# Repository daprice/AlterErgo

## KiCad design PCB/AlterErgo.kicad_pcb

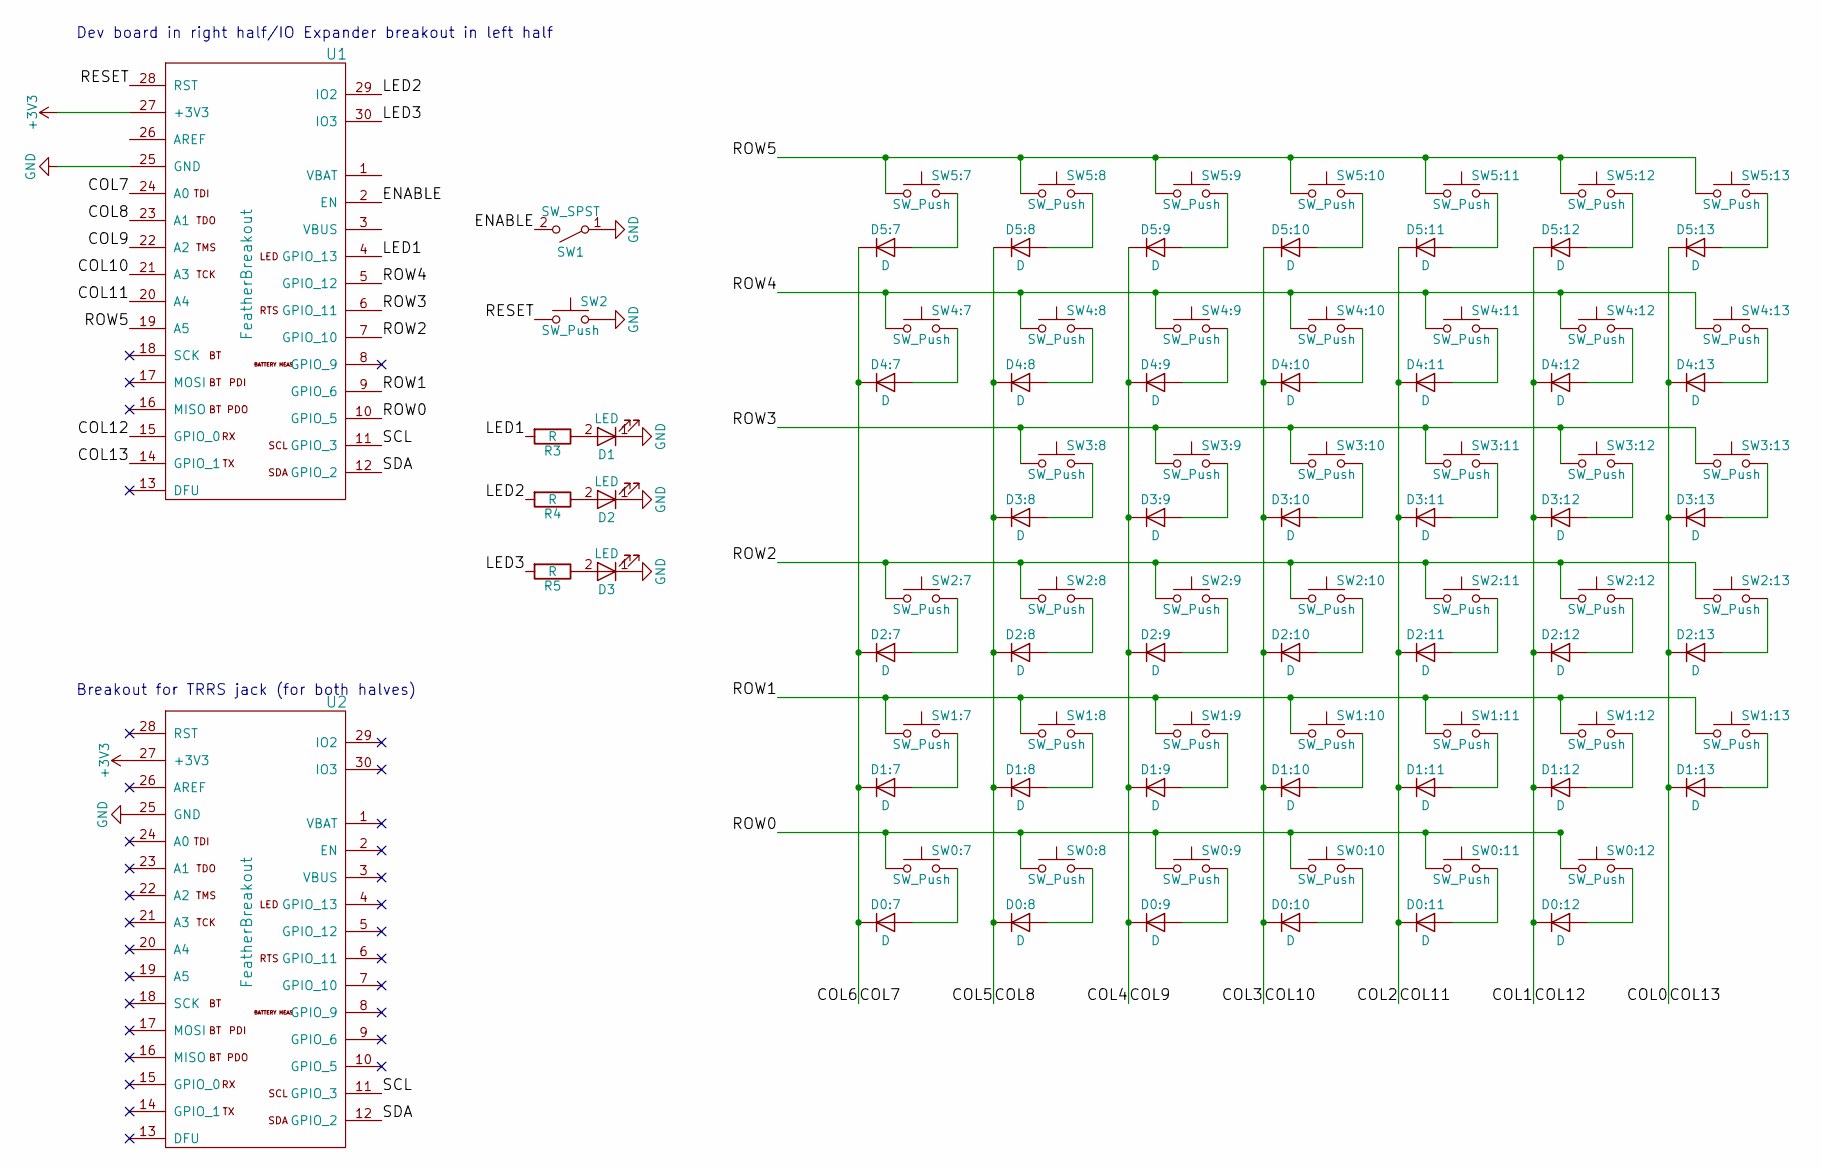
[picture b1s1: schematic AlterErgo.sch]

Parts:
D0:7, D0:8, D0:9, D0:10, D0:11, D0:12, D1:7, D1:8, D1:9, D1:10, D1:11, D1:12, D1:13, D2:7, D2:8, D2:9, D2:10, D2:11, D2:12, D2:13, D3:8, D3:9, D3:10, D3:11, D3:12, D3:13, D4:7, D4:8, D4:9, D4:10, D4:11, D4:12, D4:13, D5:7, D5:8, D5:9, D5:10, D5:11, D5:12, D5:13: D; D_SOD-123
D1, D2, D3: LED; LED_D3.0mm
R3, R4, R5: R; R_Axial_DIN0207_L6.3mm_D2.5mm_P7.62mm_Horizontal
SW0:7, SW0:8, SW0:9, SW0:10, SW0:11, SW0:12, SW1:7, SW1:8, SW1:9, SW1:10, SW1:11, SW1:12, SW1:13, SW2:7, SW2:8, SW2:9, SW2:10, SW2:11, SW2:12, SW2:13, SW3:8, SW3:9, SW3:10, SW3:11, SW3:12, SW3:13, SW4:7, SW4:8, SW4:9, SW4:10, SW4:11, SW4:12, SW4:13, SW5:7, SW5:8, SW5:9, SW5:10, SW5:11, SW5:12, SW5:13: SW_Push; Kailh_socket_optional_reversible
SW1: SW_SPST; GPTS_SPST_Pushbutton
SW2: SW_Push; SW_PUSH_6mm
U1, U2: FeatherBreakout

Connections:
+3V3: U1.27 (+3V3), U2.27 (+3V3)
/COL0: D1:13.1 (K), D2:13.1 (K), D3:13.1 (K), D4:13.1 (K), D5:13.1 (K), U1.14 (GPIO_1)
/COL1: D0:12.1 (K), D1:12.1 (K), D2:12.1 (K), D3:12.1 (K), D4:12.1 (K), D5:12.1 (K), U1.15 (GPIO_0)
/COL4: D0:9.1 (K), D1:9.1 (K), D2:9.1 (K), D3:9.1 (K), D4:9.1 (K), D5:9.1 (K), U1.22 (A2)
/COL5: D0:8.1 (K), D1:8.1 (K), D2:8.1 (K), D3:8.1 (K), D4:8.1 (K), D5:8.1 (K), U1.23 (A1)
/COL6: D0:7.1 (K), D1:7.1 (K), D2:7.1 (K), D4:7.1 (K), D5:7.1 (K), U1.24 (A0)
/COL10: D0:10.1 (K), D1:10.1 (K), D2:10.1 (K), D3:10.1 (K), D4:10.1 (K), D5:10.1 (K), U1.21 (A3)
/COL11: D0:11.1 (K), D1:11.1 (K), D2:11.1 (K), D3:11.1 (K), D4:11.1 (K), D5:11.1 (K), U1.20 (A4)
/ENABLE: SW1.2 (B), U1.2 (EN)
/LED1: R3.2, U1.4 (GPIO_13)
/LED2: R4.2, U1.29 (IO2)
/LED3: R5.2, U1.30 (IO3)
/RESET: SW2.1, U1.28 (RST)
/ROW0: SW0:7.1, SW0:8.1, SW0:9.1, SW0:10.1, SW0:11.1, SW0:12.1, U1.10 (GPIO_5); also elsewhere on the board
/ROW1: SW1:7.1, SW1:8.1, SW1:9.1, SW1:10.1, SW1:11.1, SW1:12.1, SW1:13.1, U1.9 (GPIO_6); also elsewhere on the board
/ROW2: SW2:7.1, SW2:8.1, SW2:9.1, SW2:10.1, SW2:11.1, SW2:12.1, SW2:13.1, U1.7 (GPIO_10); also elsewhere on the board
/ROW3: SW3:8.1, SW3:9.1, SW3:10.1, SW3:11.1, SW3:12.1, SW3:13.1, U1.6 (GPIO_11); also elsewhere on the board
/ROW4: SW4:7.1, SW4:8.1, SW4:9.1, SW4:10.1, SW4:11.1, SW4:12.1, SW4:13.1, U1.5 (GPIO_12); also elsewhere on the board
/ROW5: SW5:7.1, SW5:8.1, SW5:9.1, SW5:10.1, SW5:11.1, SW5:12.1, SW5:13.1, U1.19 (A5); also elsewhere on the board
/SCL: U1.11 (GPIO_3), U2.11 (GPIO_3)
/SDA: U1.12 (GPIO_2), U2.12 (GPIO_2)
GND: D1.1 (K), D2.1 (K), D3.1 (K), SW1.1 (A), SW2.2, U1.25 (GND), U2.25 (GND)
unnamed: D0:7.2 (A), SW0:7.2
unnamed: D0:8.2 (A), SW0:8.2
unnamed: D0:9.2 (A), SW0:9.2
unnamed 25: D0:10.2 (A), SW0:10.2; also elsewhere on the board
unnamed 26: D0:11.2 (A), SW0:11.2; also elsewhere on the board
unnamed: D0:12.2 (A), SW0:12.2
unnamed: D1.2 (A), R3.1
unnamed: D1:7.2 (A), SW1:7.2
unnamed: D1:8.2 (A), SW1:8.2
unnamed: D1:9.2 (A), SW1:9.2
unnamed: D1:10.2 (A), SW1:10.2
unnamed: D1:11.2 (A), SW1:11.2
unnamed: D1:12.2 (A), SW1:12.2
unnamed 35: D1:13.2 (A), SW1:13.2; also elsewhere on the board
unnamed: D2.2 (A), R4.1
unnamed: D2:7.2 (A), SW2:7.2
unnamed: D2:8.2 (A), SW2:8.2
unnamed: D2:9.2 (A), SW2:9.2
unnamed: D2:10.2 (A), SW2:10.2
unnamed: D2:11.2 (A), SW2:11.2
unnamed: D2:12.2 (A), SW2:12.2
unnamed 43: D2:13.2 (A), SW2:13.2; also elsewhere on the board
unnamed: D3.2 (A), R5.1
unnamed: D3:8.2 (A), SW3:8.2
unnamed: D3:9.2 (A), SW3:9.2
unnamed: D3:10.2 (A), SW3:10.2
unnamed: D3:11.2 (A), SW3:11.2
unnamed: D3:12.2 (A), SW3:12.2
unnamed 50: D3:13.2 (A), SW3:13.2; also elsewhere on the board
unnamed: D4:7.2 (A), SW4:7.2
unnamed: D4:8.2 (A), SW4:8.2
unnamed: D4:9.2 (A), SW4:9.2
unnamed: D4:10.2 (A), SW4:10.2
unnamed: D4:11.2 (A), SW4:11.2
unnamed: D4:12.2 (A), SW4:12.2
unnamed 57: D4:13.2 (A), SW4:13.2; also elsewhere on the board
unnamed: D5:7.2 (A), SW5:7.2
unnamed: D5:8.2 (A), SW5:8.2
unnamed: D5:9.2 (A), SW5:9.2
unnamed: D5:10.2 (A), SW5:10.2
unnamed: D5:11.2 (A), SW5:11.2
unnamed: D5:12.2 (A), SW5:12.2
unnamed 64: D5:13.2 (A), SW5:13.2; also elsewhere on the board

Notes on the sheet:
Dev board in right half/IO Expander breakout in left half
Breakout for TRRS jack (for both halves)

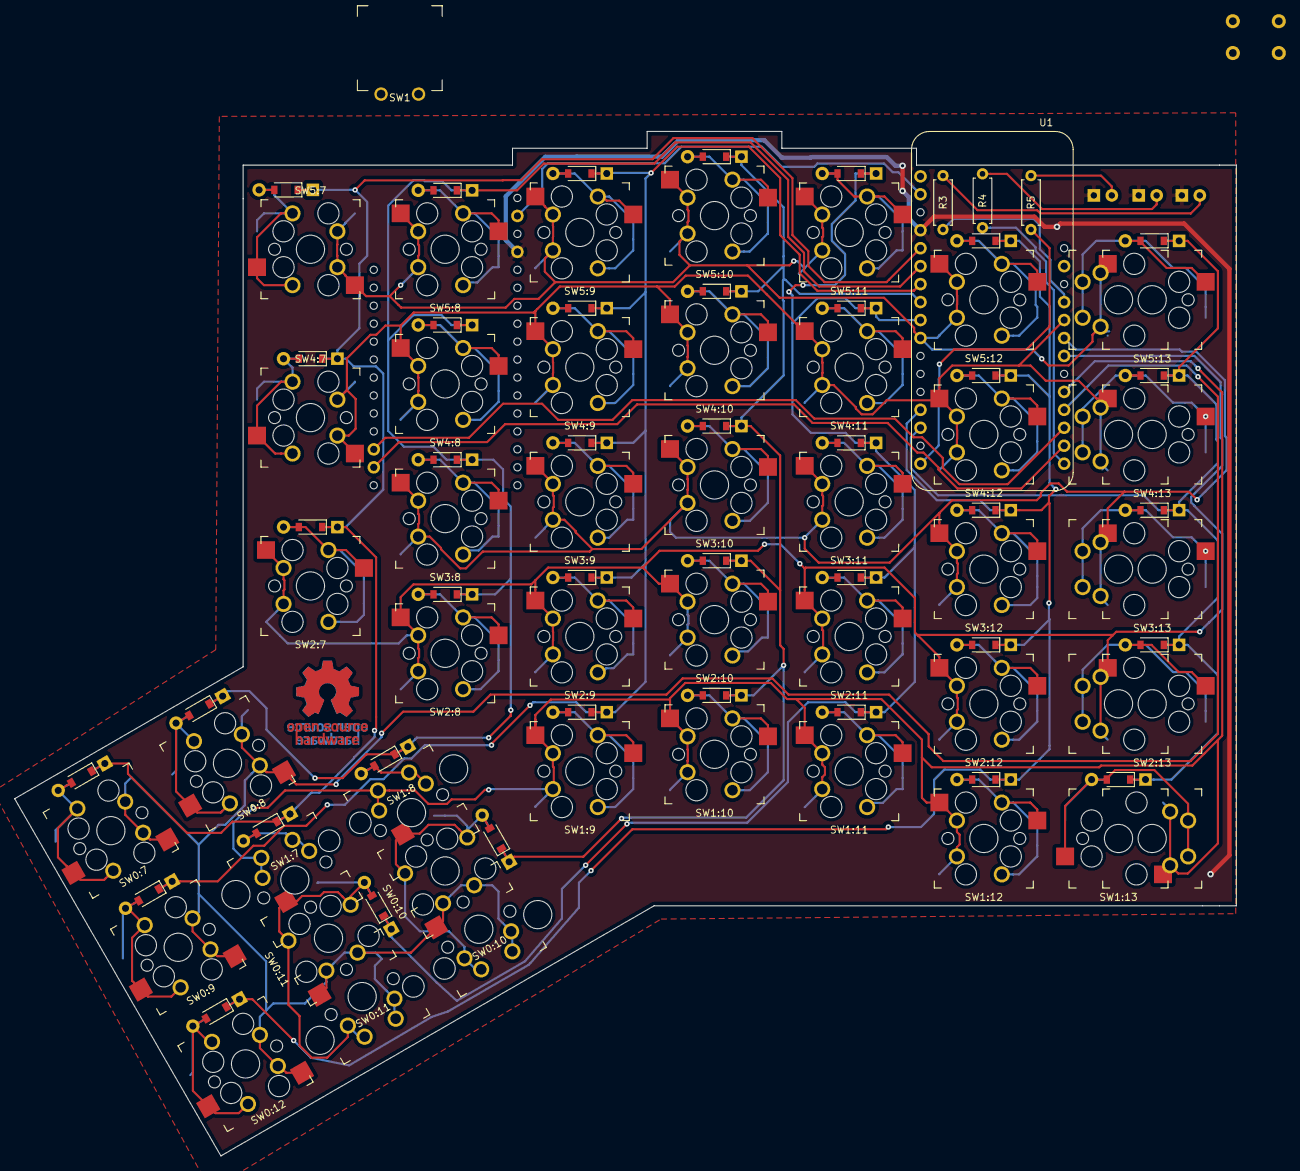
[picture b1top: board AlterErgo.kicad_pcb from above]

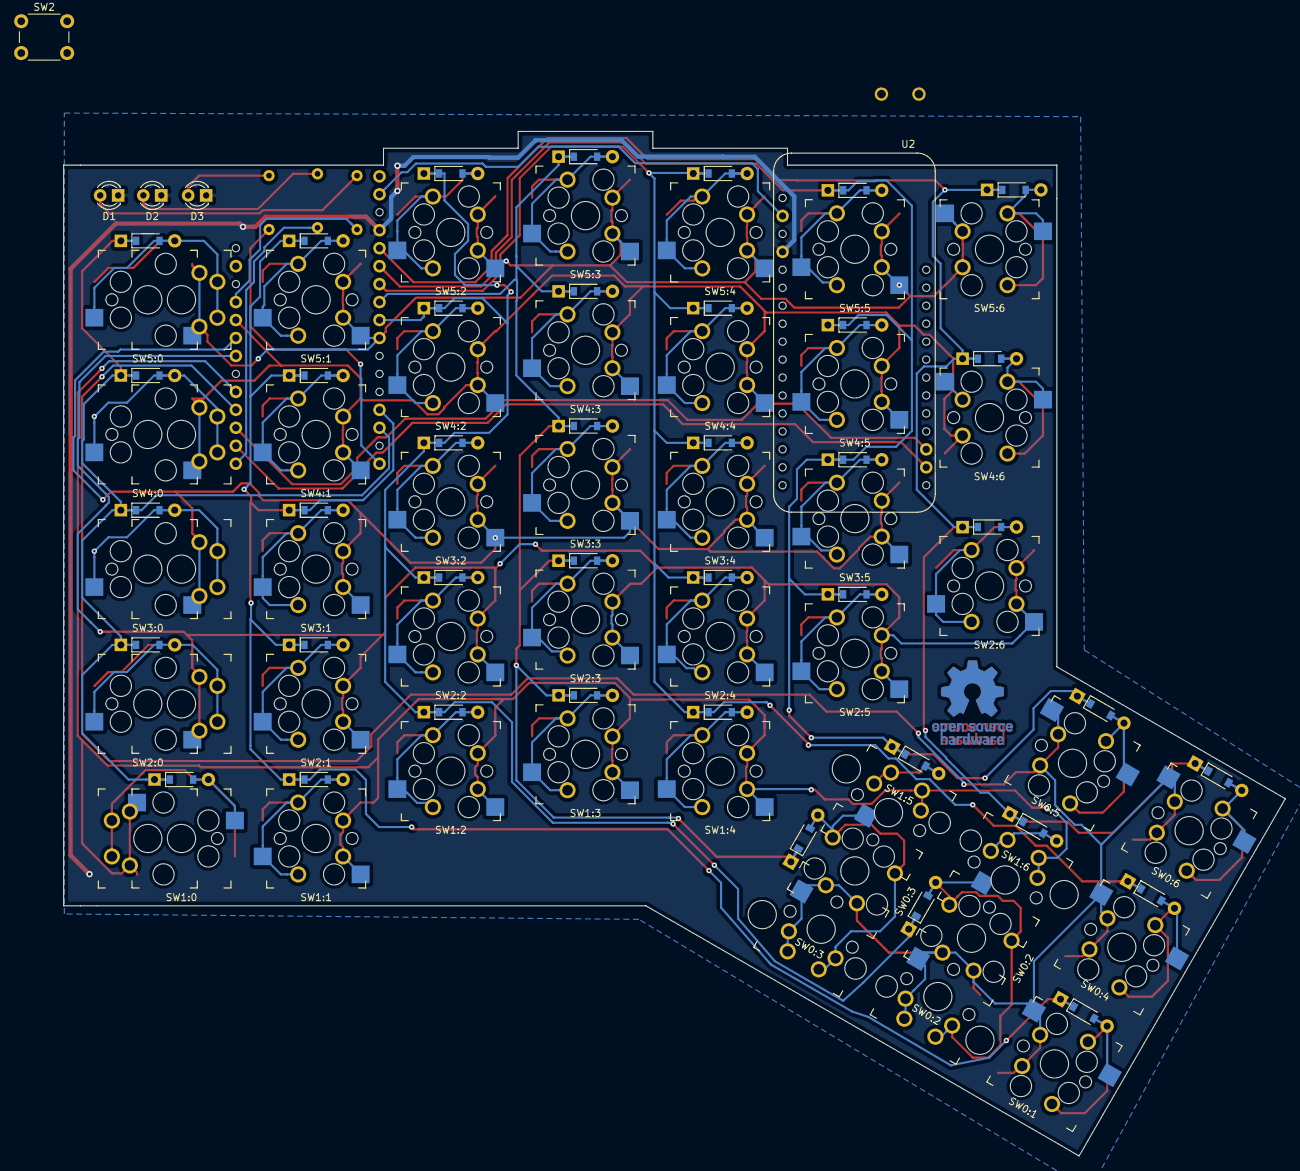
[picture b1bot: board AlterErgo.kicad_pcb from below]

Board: 2 copper layers, 172.8 x 144.9 mm, 99 parts (5 on the bottom side), 65 nets.

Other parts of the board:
SW0:10#2, SW0:11#2: SW_Push; MX_reversible
SW1:13#2, SW2:13#2, SW3:13#2, SW4:13#2, SW5:13#2: SW_Push; MX_reversible_minimal
Stab0:10, Stab0:11: SW_Stabilizer; MX_Stabilizer_2u

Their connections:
/ROW0: SW0:10#2.1, SW0:11#2.1; also elsewhere on the board
/ROW1: SW1:13#2.1; also elsewhere on the board
/ROW2: SW2:13#2.1; also elsewhere on the board
/ROW3: SW3:13#2.1; also elsewhere on the board
/ROW4: SW4:13#2.1; also elsewhere on the board
/ROW5: SW5:13#2.1; also elsewhere on the board
unnamed 25: SW0:10#2.2; also elsewhere on the board
unnamed 26: SW0:11#2.2; also elsewhere on the board
unnamed 35: SW1:13#2.2; also elsewhere on the board
unnamed 43: SW2:13#2.2; also elsewhere on the board
unnamed 50: SW3:13#2.2; also elsewhere on the board
unnamed 57: SW4:13#2.2; also elsewhere on the board
unnamed 64: SW5:13#2.2; also elsewhere on the board

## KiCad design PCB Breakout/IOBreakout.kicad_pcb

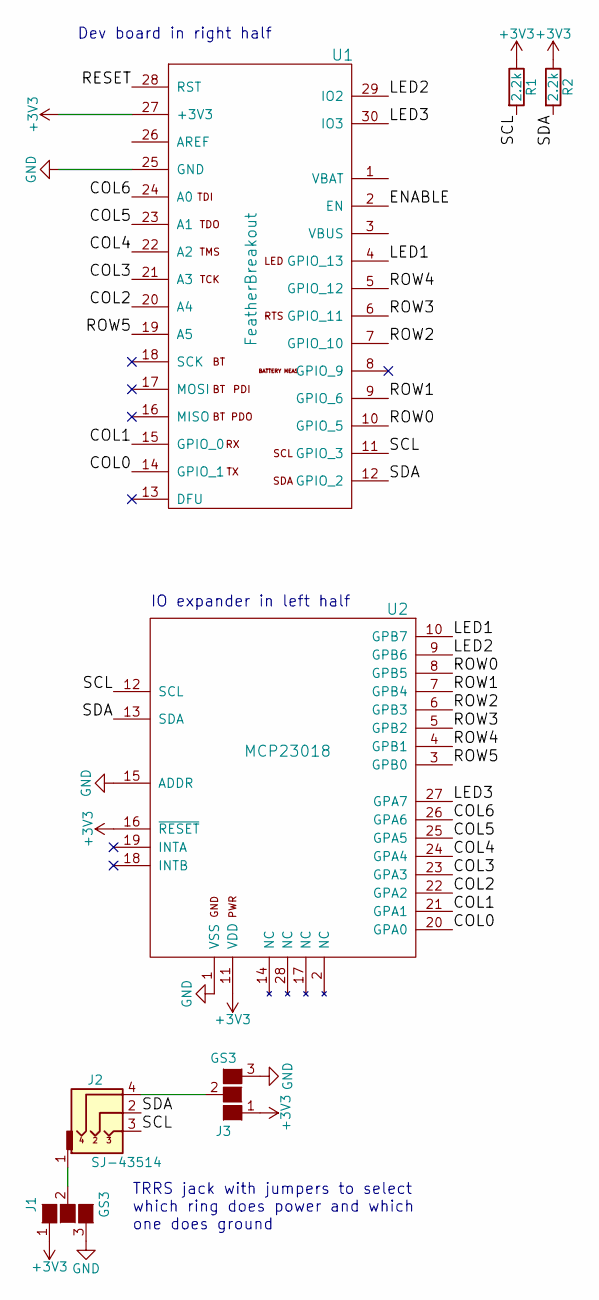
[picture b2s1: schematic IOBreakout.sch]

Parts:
J1, J3: GS3
J2: SJ-43514; TRRS_Jack_SJ-43514_reversible
R1, R2: 2.2k; R_Axial_DIN0207_L6.3mm_D2.5mm_P7.62mm_Horizontal
U1: FeatherBreakout
U2: MCP23018; DIP-28_W7.62mm

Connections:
+3V3: J1.1 (G1), J3.1 (G1), R1.1, R2.1, U1.27 (+3V3), U2.11 (VDD), U2.16 (~RESET)
/COL0: U1.14 (GPIO_1), U2.20 (GPA0)
/COL1: U1.15 (GPIO_0), U2.21 (GPA1)
/COL2: U1.20 (A4), U2.22 (GPA2)
/COL3: U1.21 (A3), U2.23 (GPA3)
/COL4: U1.22 (A2), U2.24 (GPA4)
/COL5: U1.23 (A1), U2.25 (GPA5)
/COL6: U1.24 (A0), U2.26 (GPA6)
/ENABLE: U1.2 (EN)
/LED1: U1.4 (GPIO_13), U2.10 (GPB7)
/LED2: U1.29 (IO2), U2.9 (GPB6)
/LED3: U1.30 (IO3), U2.27 (GPA7)
/RESET: U1.28 (RST)
/ROW0: U1.10 (GPIO_5), U2.8 (GPB5)
/ROW1: U1.9 (GPIO_6), U2.7 (GPB4)
/ROW2: U1.7 (GPIO_10), U2.6 (GPB3)
/ROW3: U1.6 (GPIO_11), U2.5 (GPB2)
/ROW4: U1.5 (GPIO_12), U2.4 (GPB1)
/ROW5: U1.19 (A5), U2.3 (GPB0)
/SCL: J2.3, R1.2, U1.11 (GPIO_3), U2.12 (SCL)
/SDA: J2.2, R2.2, U1.12 (GPIO_2), U2.13 (SDA)
GND: J1.3 (G3), J3.3 (G3), U1.25 (GND), U2.1 (VSS), U2.15 (ADDR)
unnamed: J1.2 (G2), J2.1
unnamed: J2.4, J3.2 (G2)

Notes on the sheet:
TRRS jack with jumpers to select which ring does power and which one does ground
IO expander in left half
Dev board in right half

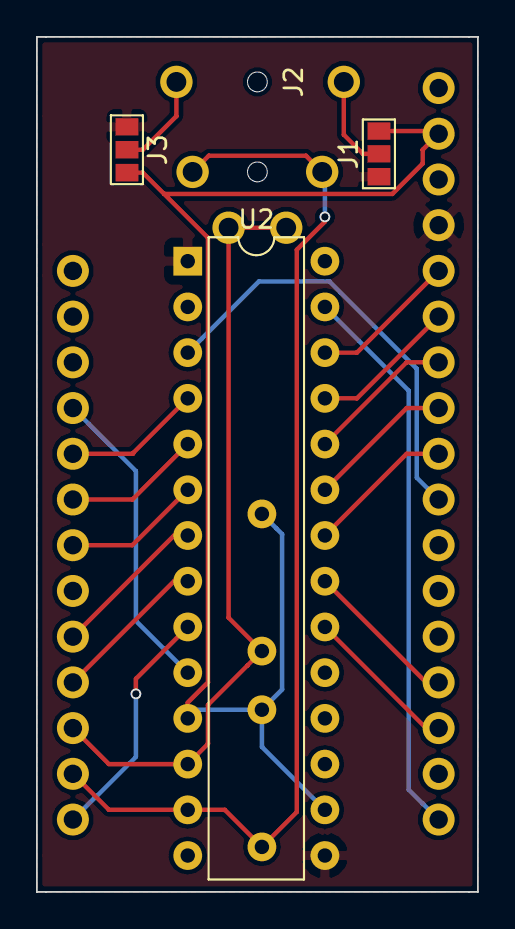
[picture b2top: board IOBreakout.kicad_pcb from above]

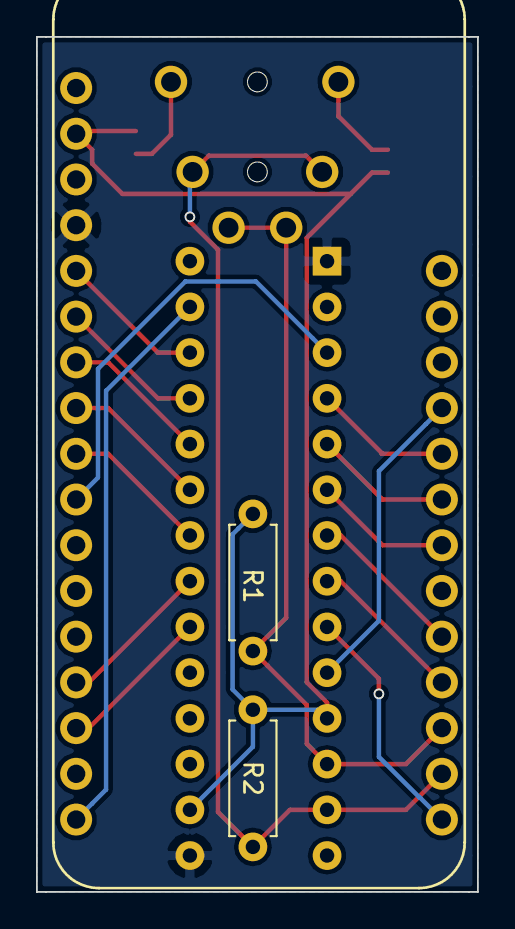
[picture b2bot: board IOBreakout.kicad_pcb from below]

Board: 2 copper layers, 24.5 x 47.5 mm, 7 parts (3 on the bottom side), 22 nets.

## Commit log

2018-03-27 Design key matrix and add necessary IC schematics
2018-04-03 Add TRRS jack to schematic; annotate matrix diodes
2018-04-09 Add .gitignore
2018-04-09 Associate most components with footprints
2018-05-15 Assign all components to footprints; generate netlist
2018-06-12 Position non-angled switches on PCB
2018-06-13 Position thumb cluster switches;
    The formulas I used to convert from Keyboard Layout Editor’s U (key units) with center of rotation to absolute coordinates in inches for KiCad can be found in https://www.icloud.com/numbers/0NN-61zf8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
2018-06-13 Allow use of 1u or 1.5u keys in all positions on outside column (using the alternate positions will require soldering and will not allow kailh sockets to be used)
2018-06-13 Set up design rules
    based on https://docs.oshpark.com/design-tools/kicad/kicad-design-rules/
2018-06-13 Add stabilizer mounting holes to 2U keys in thumb cluster
2018-06-13 Actually use .75in for key spacing (d'oh!)
2018-06-13 Avoid overlapping holes for switches that have alternate mounting options
    Unfortunately this means that the outer column will *require* socket mounting for the default positions and soldering for the alternate positions, instead of allowing either method
2018-06-13 Flip switch labels to the correct side for right hand
2018-06-14 Change diodes to use 2-sided footprint
2018-06-14 Position power switch, LEDs, TRRS jack, resistors
2018-06-14 Rework row/col pin assignments on Feather to line up better with those on the i/o expander
2018-06-14 Position diodes
2018-06-14 Hide diode reference numbers from silkscreen; add left hand side's switch reference numbers
2018-06-14 Show switch footprint graphics on both sides of the PCB
2018-06-14 Fix pin numbers to match with overlapping pads on outer row
2018-06-14 Initial attempt at routing traces in upper area
2018-06-14 Route columns
2018-06-15 Route rows
2018-06-15 Correct some vias too close to other tracks
2018-06-15 Adjust outer column socket footprint to avoid overlapping drill holes
2018-06-15 Fix some DRC errors
2018-06-15 Use non-plated thru holes (NPTH) for unused microcontroller/IO expander pins
2018-06-16 Accept through hole or surface mount 1N4148 diodes; clean up some routing slightly
2018-06-17 Add hole to allow Feather reset button to be pressed even when installed upside-down on the left-hand PCB
2018-06-17 Allow mounting of battery connector on either side of PCB
2018-06-20 Fix footprints for alternate outer column positions so kicad recognizes the pins as needing to be connected
2018-06-20 Move thumb cluster slightly
    With key wobble, the innermost 2u thumb key and the closest key in the bottom row would have probably rubbed against each other, so moved the thumb cluster outward from the rest of the keyboard sligh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
2018-07-05 Add board outline; adjust position of components; adjust routing of some traces; add ground planes; add OSHW logo
    SW1 (power toggle) was moved down to match the key spacing. TRRS jack was moved up to match the edge of the board. The traces that were moved were moved in order to allow better ground plane fill and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
2018-08-09 Remove separate battery connector points; position Feather underneath the PCB
2018-08-12 Design breakout daughterboard for IO expander/TRRS jack
2018-08-12 Update main PCB schematic to use breakout board footprint in place of controller/IO Expander and TRRS jack
2018-08-14 Route traces for Feather and breakout board in new positions
2018-09-08 Flip Feather so that the USB port is right-side-up when mounted in the right half of the keyboard
2018-09-13 Adjust some traces
2018-09-13 Adjust traces and ensure ground plane connectivity
